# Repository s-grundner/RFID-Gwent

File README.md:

# RFID-Gwent

Electronic Gwent Game from the Witcher Series

## Better Idea

- individual reading antennas
- connected to an rf-switch / multiplexer with an sma connector
- Single Controller saves cost and is easier expandable 
- maybe one module for each row is managable?

## Card Slot Reader Module PCB

| Top PCB | Bottom PCB |
|-|-|
|||

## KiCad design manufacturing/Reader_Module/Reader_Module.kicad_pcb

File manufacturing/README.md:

# RFID-Gwent

Electronic Gwent Game from the Witcher Series

## Card Slot Reader Module PCB

| Top PCB | Bottom PCB |
|-|-|
|||

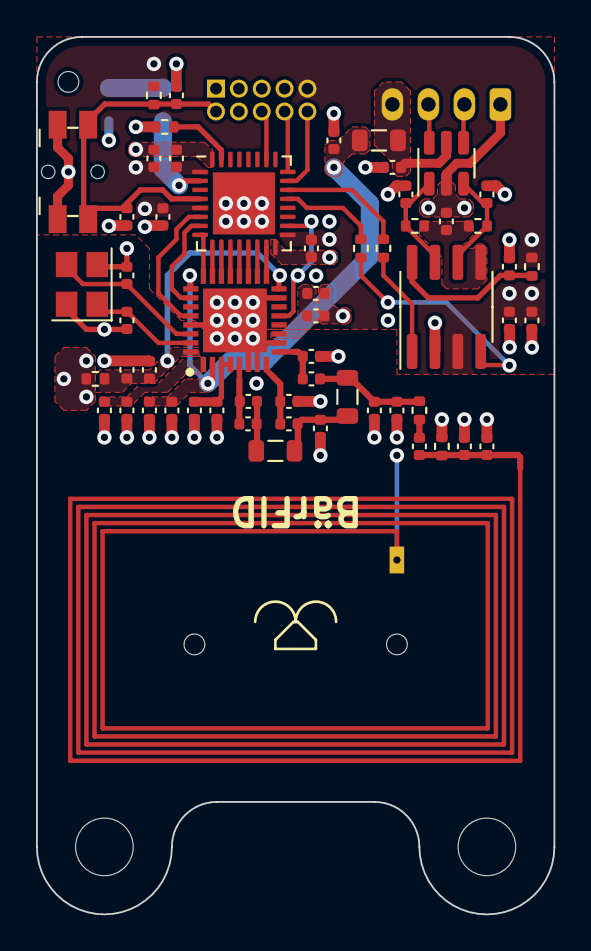
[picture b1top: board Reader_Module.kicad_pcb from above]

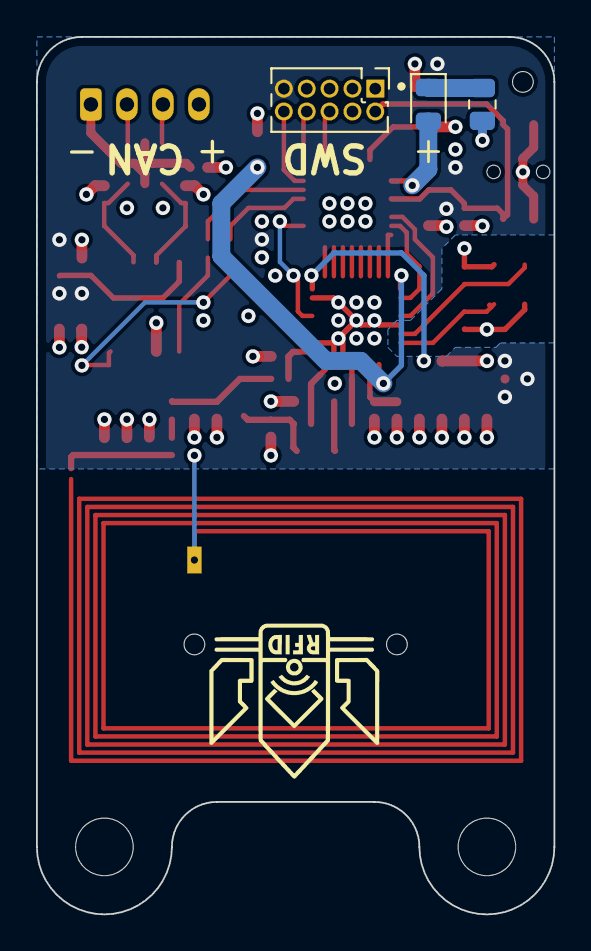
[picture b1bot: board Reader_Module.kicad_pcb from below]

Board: 4 copper layers, 28.8 x 48.8 mm, 67 parts (4 on the bottom side), 46 nets.

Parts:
AE1: Antenna_Loop; Custom_RFID_1
C1, C2, C3, C8, C20, C21, C22, C23, C24: 100n; C_0402_1005Metric
C4, C5, C7, C9, C11, C13, C15, C19, C28, C29: 2u2; C_0402_1005Metric
C6, C10, C12, C14, C16: 10n; C_0402_1005Metric
C17, C18, C26: 27p; C_0402_1005Metric
C25, C38: 47p; C_0402_1005Metric
C27: 68p; C_0402_1005Metric
C30, C32, C33: 1n2; C_0402_1005Metric
C31: 1n8; C_0402_1005Metric
C34, C36: 680p; C_0402_1005Metric
C35: 220p; C_0402_1005Metric
C37: 100p; C_0402_1005Metric
D1: TRF7964ARHBR; QFN50P500X500X100-33N-D
D2: WT; LED_0805_2012Metric
FB2: 100 @ 100MHz; L_0805_2012Metric
H3, H4: MountingHole_Pad; MountingHole_3.2mm_M3
H5, H6, H7: JLC_Tooling
J1: SW-Debug; PinHeader_2x05_P1.27mm_Vertical
J2: Conn_01x04_Pin; Molex_Micro-Latch_53254-0470_1x04_P2.00mm_Horizontal
L1, L2: 150n; L_0805_2012Metric
R1: 47k; R_0402_1005Metric
R2: 1k5; R_0805_2012Metric
R3: 100R; R_0402_1005Metric
R4: 10k; R_0402_1005Metric
R5, R6, R7, R8: 56R; R_0402_1005Metric
R9: 1k5; R_0402_1005Metric
R10: 680R; R_0402_1005Metric
R11: 0R; R_0402_1005Metric
SW1: NRST; Panasonic_EVQPUL_EVQPUC
U1: STM32L431KBU6; QFN-32-1EP_5x5mm_P0.5mm_EP3.45x3.45mm
U2: SN65HVD230; SOIC-8_3.9x4.9mm_P1.27mm
U3: USBLC6-2; SOT-23-6
Y1: 13.56MHz; Crystal_SMD_3225-4Pin_3.2x2.5mm

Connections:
+3V3: C1.2, C2.2, C3.2, C4.2, C19.1, C20.1, J1.9, R1.1, R3.1, R9.2, U1.1 (VDD), U1.5 (VDDA), U1.17 (VDD), U2.3 (VCC)
+5V: C15.2, C16.2, C28.1, D1.2 (VIN), D1.25 (EN2), FB2.1
/CAN/CAN+: C21.1, R6.2, U2.7 (CANH), U3.1
/CAN/CAN-: C23.2, R8.1, U2.6 (CANL), U3.3
/CAN/CAN_CON+: J2.3, U3.6
/CAN/CAN_CON-: J2.2, U3.4
/CAN/CAN_RS: C24.1, R9.1, U2.8 (Rs)
/CAN/CAN_RX: R7.1, U1.21 (PA11)
/CAN/CAN_TX: R5.1, U1.22 (PA12)
/CAN/CONN_5V: C29.1, FB2.2, J2.4, U3.5
/CAN/VREF: C22.1, R6.1, R8.2, U2.5 (Vref)
/MCU/NRST: C7.1, C8.2, J1.2, R1.2, SW1.2, U1.4 (NRST)
/MCU/SWCLK: J1.8, U1.24 (PA14)
/MCU/SWDIO: J1.10, U1.23 (PA13)
/MCU/SWO: J1.6, U1.26 (PB3)
/MCU/Strapping/BOOT0: R4.1, U1.31 (PH3)
/MCU/Strapping/DBG_LED: D2.2 (A), U1.2 (PC14)
/MCU/TRF_DATA_CLK: D1.26 (DATA_CLK), U1.7 (PA1)
/MCU/TRF_EN: D1.28 (EN), U1.6 (PA0)
/MCU/TRF_IO_0: D1.17 (I/O_0), U1.15 (PB1)
/MCU/TRF_IO_1: D1.18 (I/O_1), U1.14 (PB0)
/MCU/TRF_IO_2: D1.19 (I/O_2), U1.13 (PA7)
/MCU/TRF_IO_3: D1.20 (I/O_3), U1.12 (PA6)
/MCU/TRF_IO_4: D1.21 (I/O_4), U1.11 (PA5)
/MCU/TRF_IO_5: D1.22 (I/O_5), U1.10 (PA4)
/MCU/TRF_IO_6: D1.23 (I/O_6), U1.9 (PA3)
/MCU/TRF_IO_7: D1.24 (I/O_7), U1.8 (PA2)
/MCU/TRF_IRQ: D1.13 (IRQ), U1.18 (PA8)
/Matching NW/RF_RX_IN1: C32.1, C33.2, D1.8 (RX_IN1)
/Matching NW/RF_RX_IN2: C35.1, C36.2, D1.9 (RX_IN2)
/Matching NW/RF_TX_OUT: C30.1, C31.2, D1.5 (TX_OUT)
/Matching NW/SE_OUT: C27.1, R11.2
/PCB Antenna/Antenna: AE1.1, C25.1, C26.1, C27.2, R10.1
/TRF/BG: C5.2, C6.2, D1.11 (BG)
/TRF/HSE_IN: C17.2, D1.31 (OSC_IN), Y1.1
/TRF/HSE_OUT: C18.2, D1.30 (OSC_OUT), Y1.3
/TRF/VDD_A: C11.2, C12.2, D1.1 (VDD_A)
/TRF/VDD_PA: C13.2, C14.2, D1.3 (VDD_RF), D1.4 (VDD_PA)
/TRF/VDD_X: C9.2, C10.2, D1.16 (VDD_I/O), D1.32 (VDD_X), R3.2
GND: AE1.2, C1.1, C2.1, C3.1, C4.1, C5.1, C6.1, C7.2, C8.1, C9.1, C10.1, C11.1, C12.1, C13.1, C14.1, C15.1, C16.1, C17.1, C18.1, C19.2, C20.2, C21.2, C22.2, C23.1, C24.2, C25.2, C26.2, C28.2, C29.2, C33.1, C34.1, C36.1, C37.1, C38.1, D1.6 (VSS_PA), D1.7 (VSS_RX), D1.10 (VSS), D1.15 (VSS_A), D1.29 (VSS_D), D1.33 (EP), J1.1, J1.5, J1.7, J2.1, R2.2, R4.2, R10.2, SW1.1, U1.16 (VSS), U1.32 (VSS), U1.33 (VSS), U2.2 (GND), U3.2, Y1.2, Y1.4
unnamed: C30.2, C31.1, L1.1
unnamed: C32.2, C34.2, L1.2, L2.1
unnamed: C35.2, C37.2, C38.2, L2.2, R11.1
unnamed: D2.1 (K), R2.1
unnamed: R5.2, U2.1 (D)
unnamed: R7.2, U2.4 (R)

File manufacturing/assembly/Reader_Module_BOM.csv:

Comment,Designator,Footprint,LCSC
100n,"C1, C2, C3, C8, C20, C21, C22, C23, C24",Capacitor_SMD:C_0402_1005Metric,C1525
2u2,"C4, C5, C7, C9, C11, C13, C15, C19, C28, C29",Capacitor_SMD:C_0402_1005Metric,C2997286
10n,"C6, C10, C12, C14, C16",Capacitor_SMD:C_0402_1005Metric,C15195
27p,"C17, C18, C26",Capacitor_SMD:C_0402_1005Metric,C1557
47p,"C25, C38",Capacitor_SMD:C_0402_1005Metric,C1567
68p,C27,Capacitor_SMD:C_0402_1005Metric,C14441
1n2,"C30, C32, C33",Capacitor_SMD:C_0402_1005Metric,C192386
1n8,C31,Capacitor_SMD:C_0402_1005Metric,C527007
680p,"C34, C36",Capacitor_SMD:C_0402_1005Metric,C1541
220p,C35,Capacitor_SMD:C_0402_1005Metric,C1530
100p,C37,Capacitor_SMD:C_0402_1005Metric,C1546
TRF7964ARHBR,D1,QFN50P500X500X100-33N-D,C2654840
WT,D2,LED_SMD:LED_0805_2012Metric,C2296
100 @ 100MHz,FB2,Inductor_SMD:L_0805_2012Metric,C1015
150n,"L1, L2",Inductor_SMD:L_0805_2012Metric,C30618
47k,R1,Resistor_SMD:R_0402_1005Metric,C25792
1k5,"R2, R9",Resistor_SMD:R_0402_1005Metric,C25741
100R,R3,Resistor_SMD:R_0402_1005Metric,C25076
10k,R4,Resistor_SMD:R_0402_1005Metric,C25744
56R,"R5, R6, R7, R8",Resistor_SMD:R_0402_1005Metric,C25127
680R,R10,Resistor_SMD:R_0402_1005Metric,C25130
NRST,SW1,Button_Switch_SMD:Panasonic_EVQPUL_EVQPUC,C79174
STM32L431KBU6,U1,Package_DFN_QFN:QFN-32-1EP_5x5mm_P0.5mm_EP3.45x3.45mm,C2826408
SN65HVD230,U2,Package_SO:SOIC-8_3.9x4.9mm_P1.27mm,C12084
USBLC6-2,U3,Package_TO_SOT_SMD:SOT-23-6,C7519
13.56MHz,Y1,Crystal:Crystal_SMD_3225-4Pin_3.2x2.5mm,C164051

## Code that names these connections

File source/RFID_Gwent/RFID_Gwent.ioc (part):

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Mcu.Name=STM32L431K(B-C)Ux
Mcu.Package=UFQFPN32
Mcu.UserName=STM32L431KBUx
PA0.GPIOParameters=GPIO_Label
PA0.GPIO_Label=TRF_EN
PA0.Signal=GPIO_Output
PA1.GPIOParameters=GPIO_Speed,GPIO_Label
PA1.GPIO_Label=DATA_CLK
PA1.GPIO_Speed=GPIO_SPEED_FREQ_VERY_HIGH
PA1.Signal=GPIO_Output
PA10.GPIOParameters=GPIO_Label
PA10.GPIO_Label=ASK/OOK
PA10.Signal=GPIO_Output
PA11.Mode=CAN_Activate
PA11.Signal=CAN1_RX
PA12.Mode=CAN_Activate
PA12.Signal=CAN1_TX
PA13\ (JTMS-SWDIO).Mode=Trace_Asynchronous_SW
PA13\ (JTMS-SWDIO).Signal=SYS_JTMS-SWDIO
PA14\ (JTCK-SWCLK).Mode=Trace_Asynchronous_SW
PA14\ (JTCK-SWCLK).Signal=SYS_JTCK-SWCLK
PA2.GPIOParameters=GPIO_Speed,GPIO_Label
PA2.GPIO_Label=IO_7
PA2.GPIO_Speed=GPIO_SPEED_FREQ_VERY_HIGH
PA2.Signal=GPIO_Output
PA3.GPIOParameters=GPIO_Speed,GPIO_Label
PA3.GPIO_Label=IO_6
PA3.GPIO_Speed=GPIO_SPEED_FREQ_VERY_HIGH
PA3.Signal=GPIO_Output
PA4.GPIOParameters=GPIO_Speed,GPIO_Label
PA4.GPIO_Label=IO_5
PA4.GPIO_Speed=GPIO_SPEED_FREQ_VERY_HIGH
PA4.Signal=GPIO_Output
PA5.GPIOParameters=GPIO_Speed,GPIO_Label
PA5.GPIO_Label=IO_4
PA5.GPIO_Speed=GPIO_SPEED_FREQ_VERY_HIGH
PA5.Signal=GPIO_Output
PA6.GPIOParameters=GPIO_Speed,GPIO_Label
PA6.GPIO_Label=IO_3
PA6.GPIO_Speed=GPIO_SPEED_FREQ_VERY_HIGH
PA6.Signal=GPIO_Output
PA7.GPIOParameters=GPIO_Speed,GPIO_Label
PA7.GPIO_Label=IO_2
PA7.GPIO_Speed=GPIO_SPEED_FREQ_VERY_HIGH
PA7.Signal=GPIO_Output
PA8.GPIOParameters=GPIO_Label
PA8.GPIO_Label=MOD
PA8.Signal=GPIO_Output
PA9.GPIOParameters=GPIO_Label
PA9.GPIO_Label=IRQ
PA9.Signal=GPXTI9
PB0.GPIOParameters=GPIO_Speed,GPIO_Label
PB0.GPIO_Label=IO_1
PB0.GPIO_Speed=GPIO_SPEED_FREQ_VERY_HIGH
PB0.Signal=GPIO_Output
PB1.GPIOParameters=GPIO_Speed,GPIO_Label
PB1.GPIO_Label=IO_0
PB1.GPIO_Speed=GPIO_SPEED_FREQ_VERY_HIGH
PB1.Signal=GPIO_Output
PB3\ (JTDO-TRACESWO).Mode=Trace_Asynchronous_SW
PB3\ (JTDO-TRACESWO).Signal=SYS_JTDO-SWO
PC14-OSC32_IN\ (PC14).Signal=GPIO_Output
PH3-BOOT0.GPIOParameters=GPIO_Label
PH3-BOOT0.GPIO_Label=BOOT0
PH3-BOOT0.Signal=GPIO_Input
RCC.HSE_VALUE=8000000
RCC.SYSCLKFreq_VALUE=80000000
RCC.SYSCLKSource=RCC_SYSCLKSOURCE_PLLCLK
board=custom

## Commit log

2023-01-23 created template
2023-01-25 added info sources
2023-02-01 added datasheets for useful ics
2023-02-01 added references
2023-08-14 upd docs
2023-08-14 Source Generation and Pinout Config
2023-08-14 New Schematic
    PCB Antenna and Matching not yet implemented
2023-08-14 New PCB
    PCB Antenna and Matching not yet implemented
2023-08-16 added reference designs and Application notes
2023-08-16 Antenna Matching
2023-08-16 upd pinout
2023-08-16 added Matching NW to Schematic
2023-08-16 Update PCB
    Added Supplyline filtering
2023-08-16 added PCB Images
2023-08-16 cleanup
2023-08-17 upd documentation
2023-08-25 upd board
2025-06-01 rm redundant test firmware
